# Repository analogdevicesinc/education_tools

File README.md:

# ADI Educational Content

[Analog Devices Inc.](https://www.analog.com/en/index.html)

Resource files for applications/examples with Active Learning Modules [ADALM1000](https://www.analog.com/en/design-center/evaluation-hardware-and-software/evaluation-boards-kits/adalm1000.html), [ADALM2000](https://www.analog.com/en/design-center/evaluation-hardware-and-software/evaluation-boards-kits/adalm2000.html), [ADALM-PLUTO](https://www.analog.com/en/design-center/evaluation-hardware-and-software/evaluation-boards-kits/adalm-pluto.html) and [ADALP2000](https://www.analog.com/en/design-center/evaluation-hardware-and-software/evaluation-boards-kits/EVAL-ADALP2000.html) Parts Kit.

Most of the files are linked as archives to the activities available in the [Analog Devices Engineering University Program](https://wiki.analog.com/university).

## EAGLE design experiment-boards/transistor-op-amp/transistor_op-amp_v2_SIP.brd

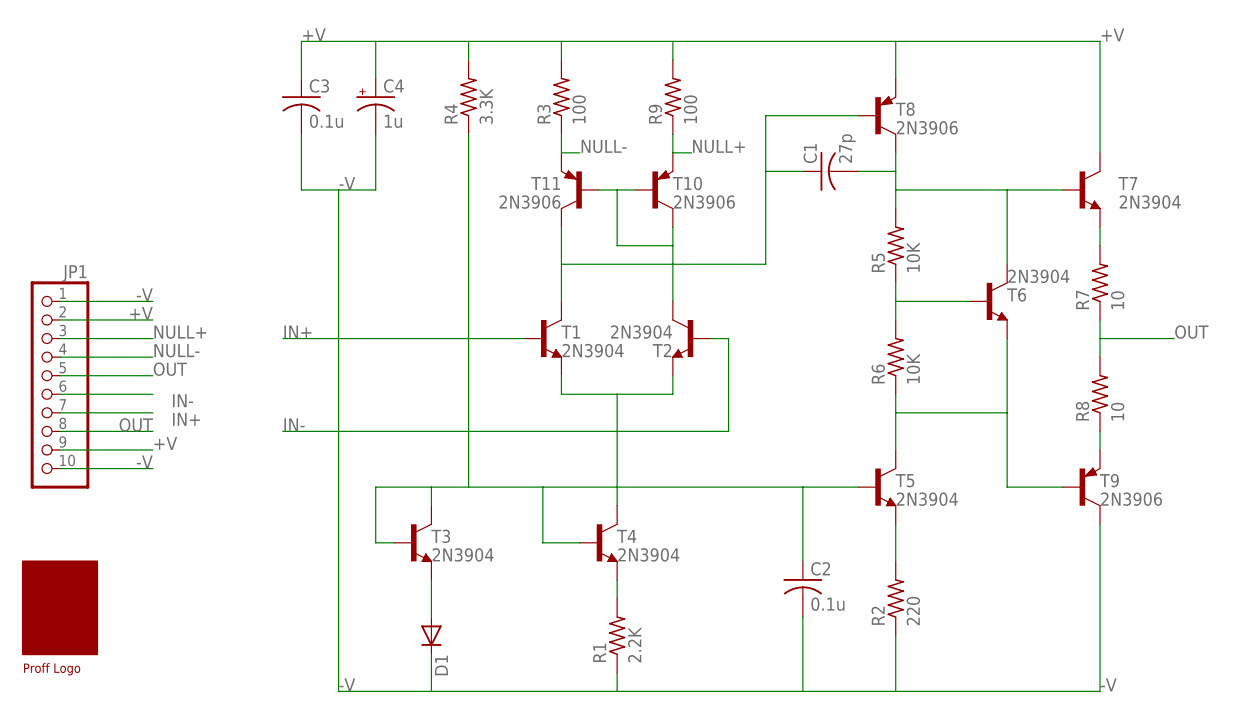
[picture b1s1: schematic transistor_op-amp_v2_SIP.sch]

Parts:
C1: 27p; C050-024X044
C2, C3: 0.1u; C050-024X044
C4: 1u; E2,5-5
D1: DIODE-D-7.5; D-7.5
JP1: PINHD-1X10; 1X10
R1: 2.2K; 0207/7
R2: 220; 0207/7
R3, R9: 100; 0207/7
R4: 3.3K; 0207/7
R5, R6: 10K; 0207/7
R7, R8: 10; 0207/7
T1, T2, T3, T4, T5, T6, T7: 2N3904; TO92
T8, T9, T10, T11: 2N3906; TO92
U$1: PROFF

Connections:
+V: C3.1, C4.+, JP1.2, JP1.9, R3.2, R4.2, R9.2, T7.1 (C), T8.3 (E)
-V: C2.2, C3.2, C4.-, D1.C, JP1.1, JP1.10, R1.1, R2.1, T9.1 (C)
IN+: JP1.6, T1.2 (B)
IN-: JP1.7, T2.2 (B)
unnamed: D1.A, T3.3 (E)
unnamed: C2.1, R4.1, T3.1 (C), T3.2 (B), T4.2 (B), T5.2 (B)
unnamed: R1.2, T4.3 (E)
unnamed: R2.2, T5.3 (E)
unnamed: T1.3 (E), T2.3 (E), T4.1 (C)
unnamed: R7.2, T7.3 (E)
unnamed: R6.1, T5.1 (C), T6.3 (E), T9.2 (B)
unnamed: R5.1, R6.2, T6.2 (B)
unnamed: C1.2, R5.2, T6.1 (C), T7.2 (B), T8.1 (C)
unnamed: R8.1, T9.3 (E)
unnamed: C1.1, T1.1 (C), T8.2 (B), T11.1 (C)
unnamed: T2.1 (C), T10.1 (C), T10.2 (B), T11.2 (B)
NULL+: JP1.3, R9.1, T10.3 (E)
NULL-: JP1.4, R3.1, T11.3 (E)
OUT: JP1.5, JP1.8, R7.1, R8.2

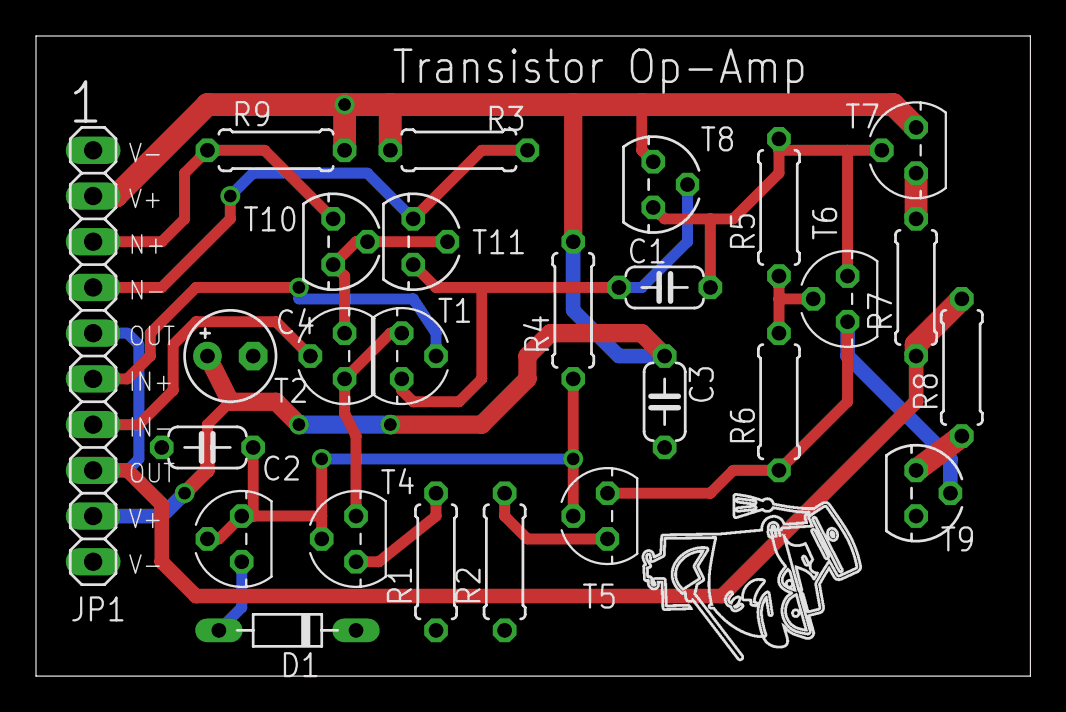
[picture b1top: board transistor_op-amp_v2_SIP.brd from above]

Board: 2 copper layers, 55.2 x 35.6 mm, 27 parts (0 on the bottom side), 19 nets.

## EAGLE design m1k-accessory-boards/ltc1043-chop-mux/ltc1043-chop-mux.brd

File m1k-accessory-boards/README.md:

# ADALM1000 Accessory Boards

[Analog Devices Inc.](https://www.analog.com/en/index.html)

Design Resource files for accessory PC boards for use with Active Learning Module [ADALM1000](https://www.analog.com/en/design-center/evaluation-hardware-and-software/evaluation-boards-kits/adalm1000.html), [ADALP2000](https://www.analog.com/en/design-center/evaluation-hardware-and-software/evaluation-boards-kits/EVAL-ADALP2000.html) Parts Kit.

The PC Board design files were generated using EAGLE (Easily Applicable Graphical Layout Editor) Version 7.7.0 for Windows (64 bit) Standard Edition.

The board files can generally be downloaded and used directly on many prototyping and rapid PC board manufacturer web sites. [Oshpark](https://oshpark.com/):

General background on the M1K accessory boards.

The idea is that the M1K analog input path is bare bones simple (for cost savings) and this ecosystem of accessory boards is a set of signal chain building blocks to daisy chain together more complex input and output signal chains. To that end there are generally pass through connections from one side of the boards to the other. Let's consider the 8 pin female analog connector on the M1K as connector "analog1". The connector pads on the accessory boards named ADALM1000 would be populated with matching male connectors. The connector pads on the accessory boards named analog2 would be populated with a female connector replicating the female connector on the M1K but with whatever signal processing a given board does inserted. The simple model is that various boards would be daisy chained in series (the ADALM1000 male connector plugged into the analog2 female connector etc.) building up a new signal chain. The order the boards are connected in series would of course matter and provides additional flexibility. What is not yet there in the initial release is what we are calling a "riser" board which allows the signal chain to split vertically and have a second parallel path as it were.

- Applications:
  - Analog Input Multiplexer using CD4052 dual 4:1
  - Input Buffer amplifier using dual op-amp footprint such as AD822 and AD8542
  - Input Buffer amplifier using single op-amp footprints
  - Input resistor voltage divider
  - Floating Amp meter / Milli-ohm meter
  - BNC / Scope probe adapter
  - +/- 5 V supply generator
    - Notice that the M1K connector has two ground pins. The -5 generator hijacks one of these pins for its -5 V rail. On all the accessory boards these two "ground" pins are never shorted together. If a given board (other than the -5 generator) is plugged into the M1K directly, the two pins will be connected together inside the M1K.
  - AWG quad op-amp buffer
  - Second order active filter
  - Test point extender board
  - Right angle extender board
  - Dip Switch extender board

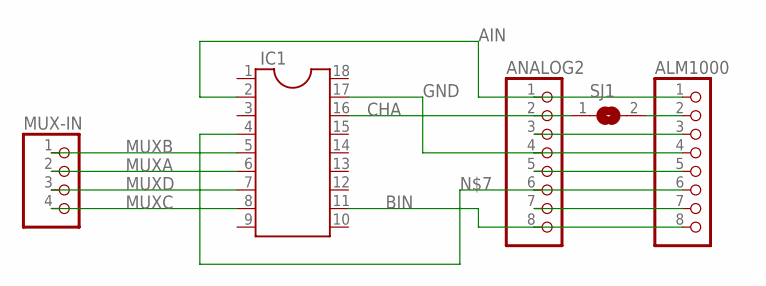
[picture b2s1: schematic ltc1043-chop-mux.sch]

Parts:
ALM1000: PINHD-1X8; 1X08
ANALOG2: PINHD-1X8; 1X08
IC1: DIL18
MUX-IN: PINHD-1X4; 1X04
SJ1: SJ

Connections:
AIN: ALM1000.1, ANALOG2.1, IC1.2
BIN: ALM1000.8, ANALOG2.8, IC1.11
CHA: ANALOG2.2, IC1.16, SJ1.1
GND: ALM1000.4, ANALOG2.4, IC1.17
MUXA: IC1.6, MUX-IN.2
MUXB: IC1.5, MUX-IN.1
MUXC: IC1.8, MUX-IN.4
MUXD: IC1.7, MUX-IN.3
unnamed: ALM1000.2, SJ1.2
unnamed: ALM1000.7, ANALOG2.7
unnamed: ALM1000.6, ANALOG2.6, IC1.4
unnamed: ALM1000.5, ANALOG2.5
unnamed: ALM1000.3, ANALOG2.3

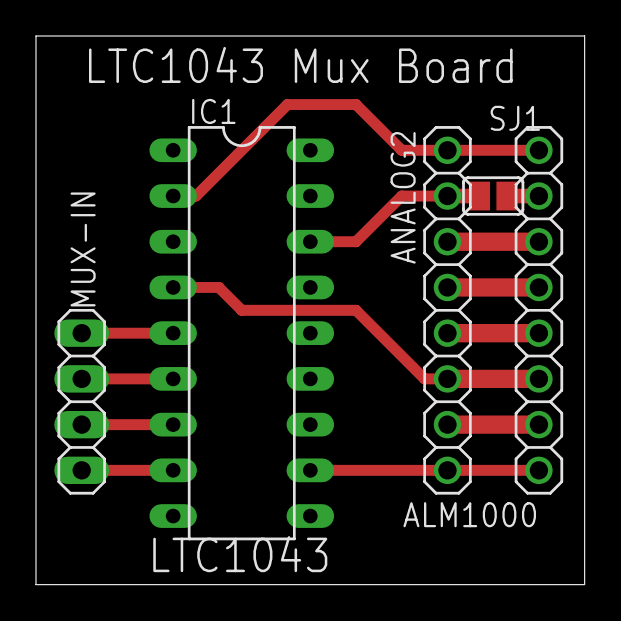
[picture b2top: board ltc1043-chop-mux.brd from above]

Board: 2 copper layers, 30.5 x 30.5 mm, 5 parts (0 on the bottom side), 13 nets.

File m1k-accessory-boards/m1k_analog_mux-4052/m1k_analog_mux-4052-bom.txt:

Partlist exported from m1k_analog_mux-4052.sch at 4/23/2020 8:47 AM

Part    Value   Device      Package Description                       
ALM1000         PINHD-1X8   1X08    PIN HEADER                        
ANALOG2         PINHD-1X8   1X08    PIN HEADER                        
CTRL            PINHD-1X3   1X03    PIN HEADER                        
IC1     CD4052N CD4052N     DIL16   Dual 4-channel ANALOG MULTIPLEXER 
MUXIN           PINHD-1X8   1X08    PIN HEADER

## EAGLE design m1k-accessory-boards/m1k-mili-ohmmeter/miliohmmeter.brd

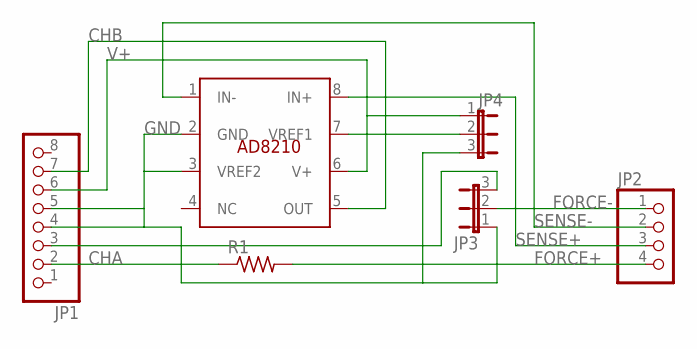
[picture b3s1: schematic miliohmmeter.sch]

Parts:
JP1: PINHD-1X8; 1X08
JP2: PINHD-1X4; 1X04
JP3, JP4: JP2E; JP2
R1: R-US_0207/10; 0207/10
U1: AD8210; SO8

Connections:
CHA: JP1.2, R1.1
CHB: JP1.7, U1.5 (OUT)
FORCE+: JP2.4, R1.2
FORCE-: JP2.1, JP3.2
GND: JP1.4, JP1.5, JP3.1, JP4.3, U1.2 (GND), U1.3 (VREF2)
unnamed: JP1.3, JP3.3
unnamed: JP4.2, U1.7 (VREF1)
SENSE+: JP2.3, U1.8 (IN+)
SENSE-: JP2.2, U1.1 (IN-)
V+: JP1.6, JP4.1, U1.6 (V+)

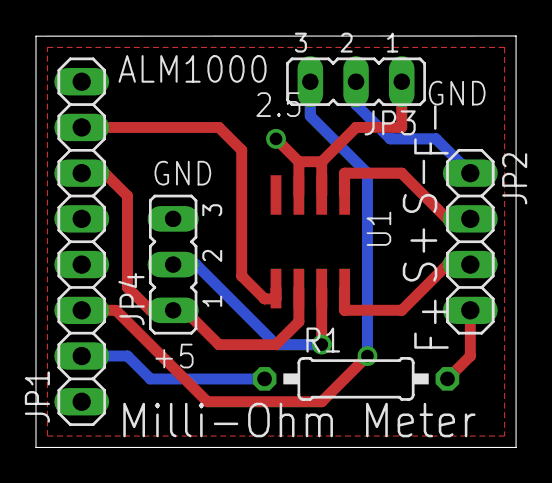
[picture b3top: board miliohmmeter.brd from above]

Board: 2 copper layers, 26.7 x 22.9 mm, 6 parts (0 on the bottom side), 10 nets.

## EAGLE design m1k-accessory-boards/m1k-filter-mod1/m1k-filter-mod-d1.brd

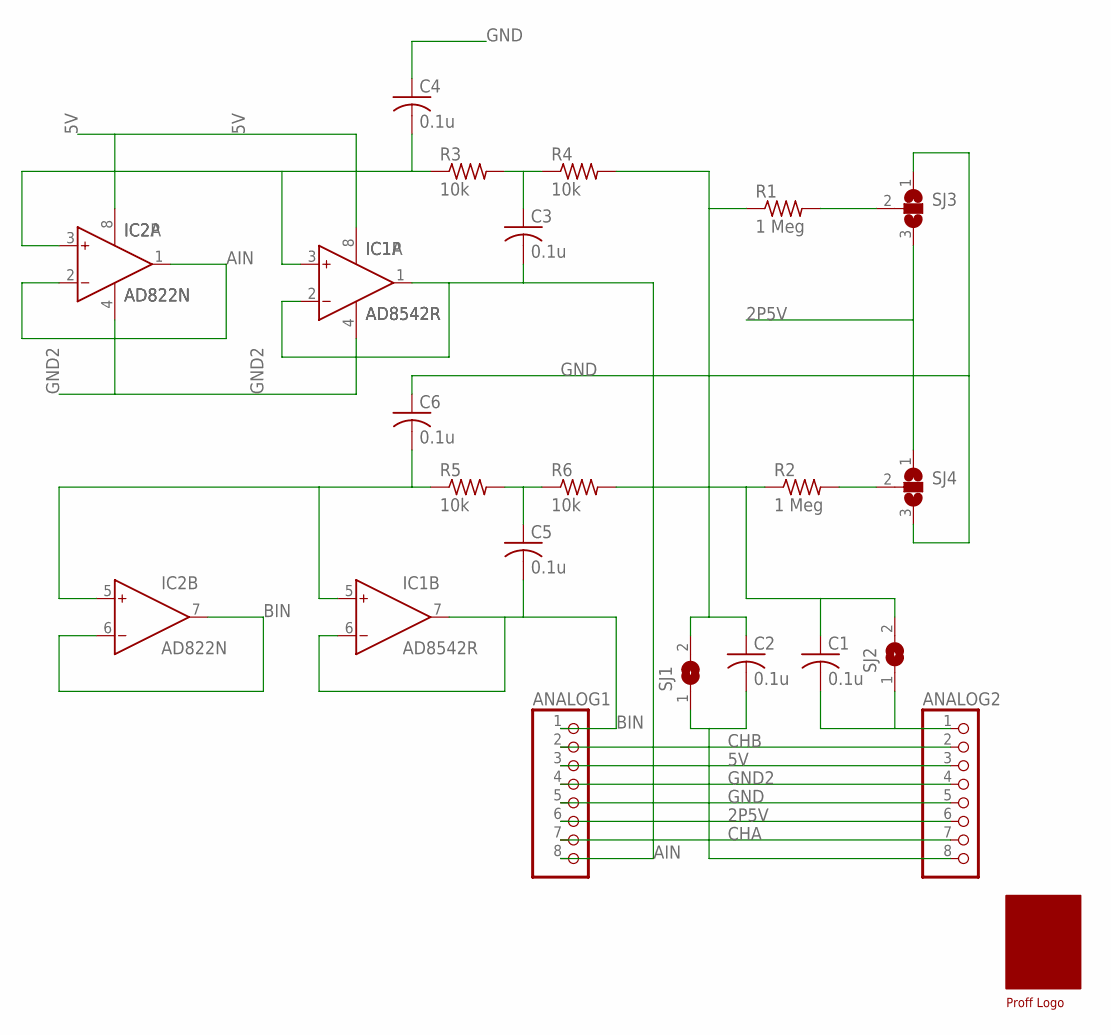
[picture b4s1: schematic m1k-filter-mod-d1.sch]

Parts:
ANALOG1, ANALOG2: PINHD-1X8; 1X08
C1, C2, C3, C4, C5, C6: 0.1u; C050-024X044
IC1: AD8542R; SO8
IC2: AD822N; DIL08
R1, R2: 1 Meg; 0204/7
R3, R4, R5, R6: 10k; 0204/7
SJ1, SJ2: SJ
SJ3, SJ4: SJ2W; SJ_2
U$1: PROFF

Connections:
2P5V: ANALOG1.6, ANALOG2.6, SJ3.3, SJ4.1
5V: ANALOG1.3, ANALOG2.3, IC1.8 (V+), IC2.8 (V+)
AIN: ANALOG1.8, C3.2, IC1.1 (OUT), IC1.2 (IN-), IC2.1 (OUT), IC2.2 (IN-)
BIN: ANALOG1.1, C5.2, IC1.6 (IN-), IC1.7 (OUT), IC2.6 (IN-), IC2.7 (OUT)
CHA: ANALOG1.7, ANALOG2.7
CHB: ANALOG1.2, ANALOG2.2
GND: ANALOG1.5, ANALOG2.5, C4.1, C6.1, SJ3.1, SJ4.3
GND2: ANALOG1.4, ANALOG2.4, IC1.4 (V-), IC2.4 (V-)
unnamed: ANALOG2.1, C1.2, SJ2.1
unnamed: R1.2, SJ3.2
unnamed: ANALOG2.8, C2.2, SJ1.1
unnamed: C3.1, R3.2, R4.1
unnamed: C2.1, R1.1, R4.2, SJ1.2
unnamed: C1.1, R2.1, R6.2, SJ2.2
unnamed: C6.2, IC1.5 (IN+), IC2.5 (IN+), R5.1
unnamed: C5.1, R5.2, R6.1
unnamed: C4.2, IC1.3 (IN+), IC2.3 (IN+), R3.1
unnamed: R2.2, SJ4.2

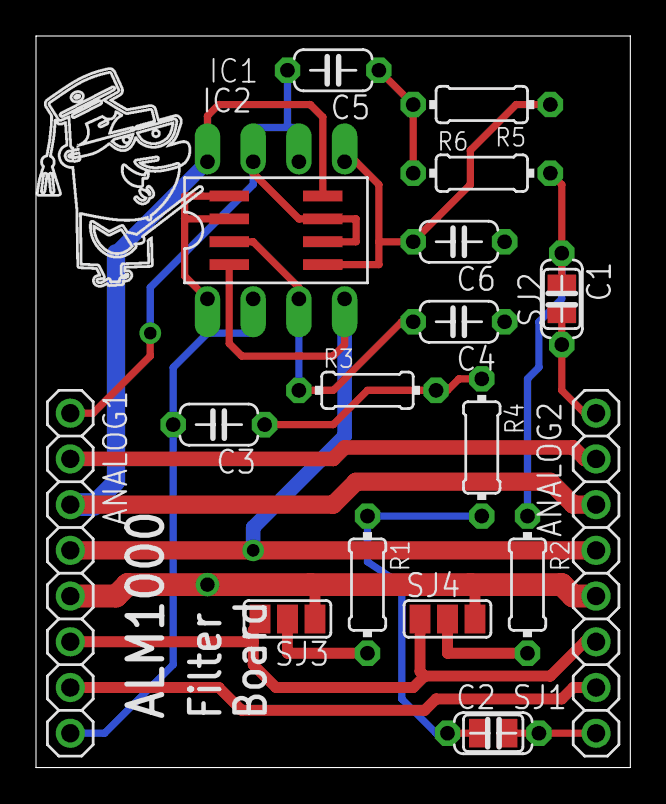
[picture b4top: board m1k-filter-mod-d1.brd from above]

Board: 2 copper layers, 33.0 x 40.6 mm, 21 parts (0 on the bottom side), 18 nets.

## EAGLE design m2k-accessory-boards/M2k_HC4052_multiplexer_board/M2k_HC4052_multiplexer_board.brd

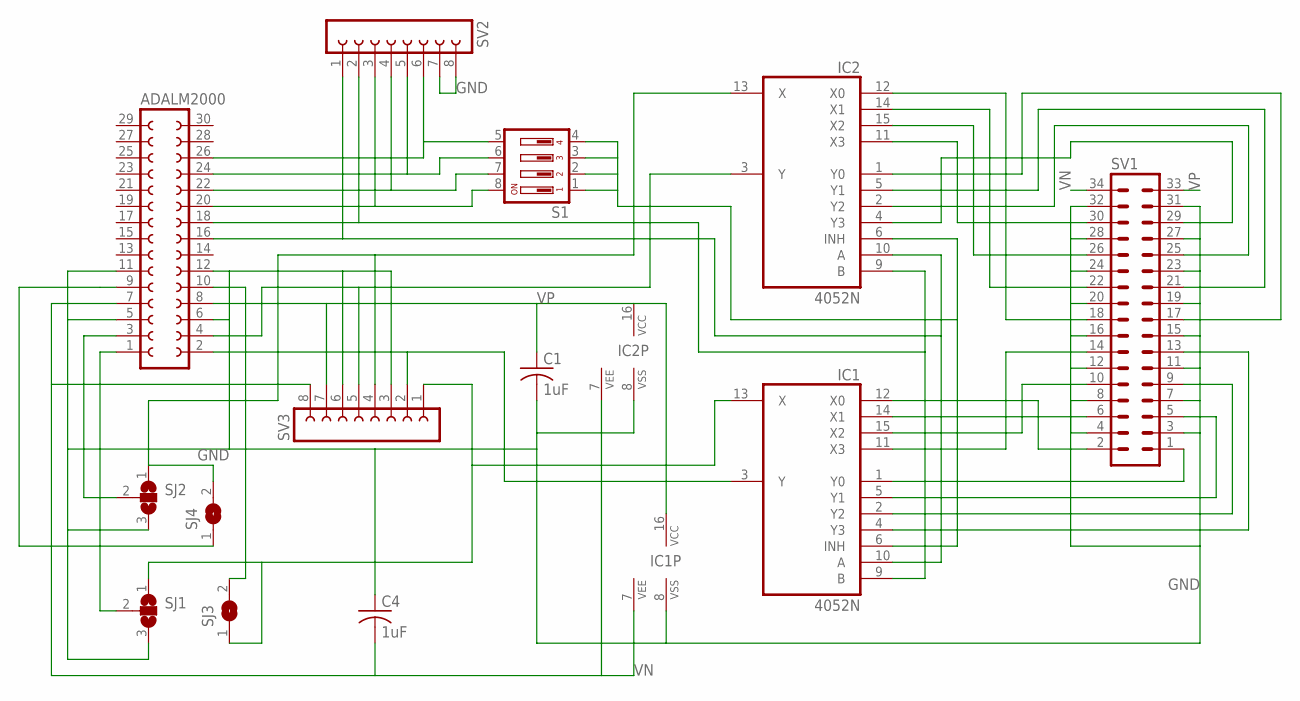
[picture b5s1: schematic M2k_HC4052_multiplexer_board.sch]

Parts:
ADALM2000: FE15-2
C1, C4: 1uF; C050-024X044
IC1, IC2: 4052N; DIL16
S1: DIP04YL
SJ1, SJ2: SJ2W; SJ_2
SJ3, SJ4: SJ
SV1: MA17-2
SV2, SV3: FE08-1; FE08

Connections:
ES: IC1.13 (X), SJ1.1, SJ3.1, SV3.1
GND: ADALM2000.5, ADALM2000.6, ADALM2000.11, ADALM2000.12, C1.2, C4.1, IC1.8 (VSS), IC2.8 (VSS), SJ1.3, SJ2.3, SV1.3, SV1.4, SV1.7, SV1.8, SV1.11, SV1.12, SV1.15, SV1.16, SV1.19, SV1.20, SV1.23, SV1.24, SV1.27, SV1.28, SV1.31, SV1.32, SV2.7, SV2.8, SV3.3, SV3.6
unnamed: ADALM2000.26, S1.5, SV2.6
unnamed: IC1.12 (X0), SV1.2
unnamed: IC1.6 (INH), IC2.6 (INH), S1.1, S1.2, S1.3, S1.4
unnamed: ADALM2000.2, IC1.3 (Y), SV3.2
unnamed: IC1.1 (Y0), SV1.1
unnamed: IC1.14 (X1), SV1.6
unnamed: IC2.13 (X), SJ2.1, SJ4.2, SV3.4
unnamed: IC1.5 (Y1), SV1.5
unnamed: IC1.15 (X2), SV1.10
unnamed: ADALM2000.4, IC2.3 (Y), SV3.5
unnamed: ADALM2000.16, IC1.10 (A), IC2.10 (A), SV2.1
unnamed: ADALM2000.18, IC1.9 (B), IC2.9 (B), SV2.2
unnamed: IC1.11 (X3), SV1.14
unnamed: IC1.2 (Y2), SV1.9
unnamed: IC1.4 (Y3), SV1.13
unnamed: IC2.12 (X0), SV1.18
unnamed: IC2.14 (X1), SV1.22
unnamed: IC2.15 (X2), SV1.26
unnamed: IC2.11 (X3), SV1.30
unnamed: IC2.1 (Y0), SV1.17
unnamed: IC2.5 (Y1), SV1.21
unnamed: IC2.2 (Y2), SV1.25
unnamed: IC2.4 (Y3), SV1.29
unnamed: ADALM2000.1, SJ1.2
unnamed: ADALM2000.3, SJ2.2
unnamed: ADALM2000.20, S1.8, SV2.3
unnamed: ADALM2000.22, S1.7, SV2.4
unnamed: ADALM2000.24, S1.6, SV2.5
VN: ADALM2000.7, C4.2, IC1.7 (VEE), IC2.7 (VEE), SV1.34, SV3.8
VP: ADALM2000.8, C1.1, IC1.16 (VCC), IC2.16 (VCC), SV1.33, SV3.7
W1: ADALM2000.10, SJ3.2
W2: ADALM2000.9, SJ4.1

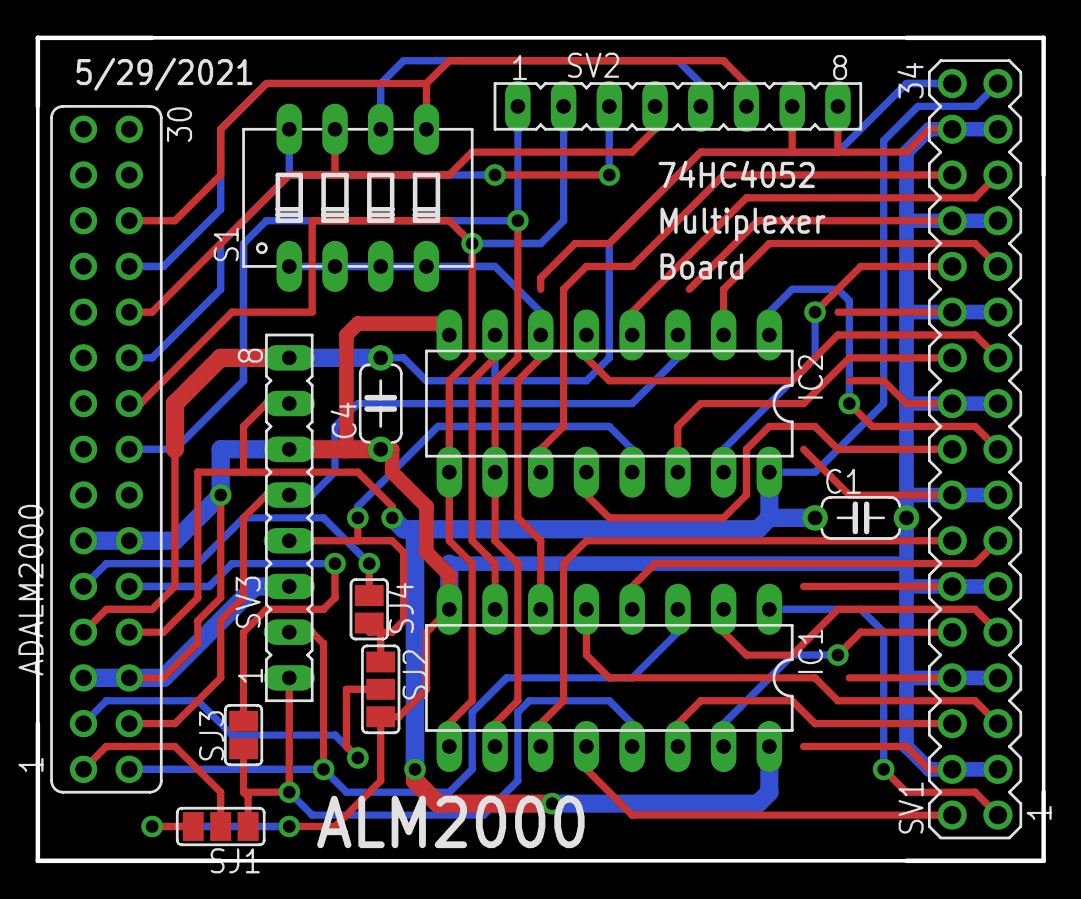
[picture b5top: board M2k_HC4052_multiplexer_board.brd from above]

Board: 2 copper layers, 55.9 x 45.7 mm, 13 parts (0 on the bottom side), 34 nets.

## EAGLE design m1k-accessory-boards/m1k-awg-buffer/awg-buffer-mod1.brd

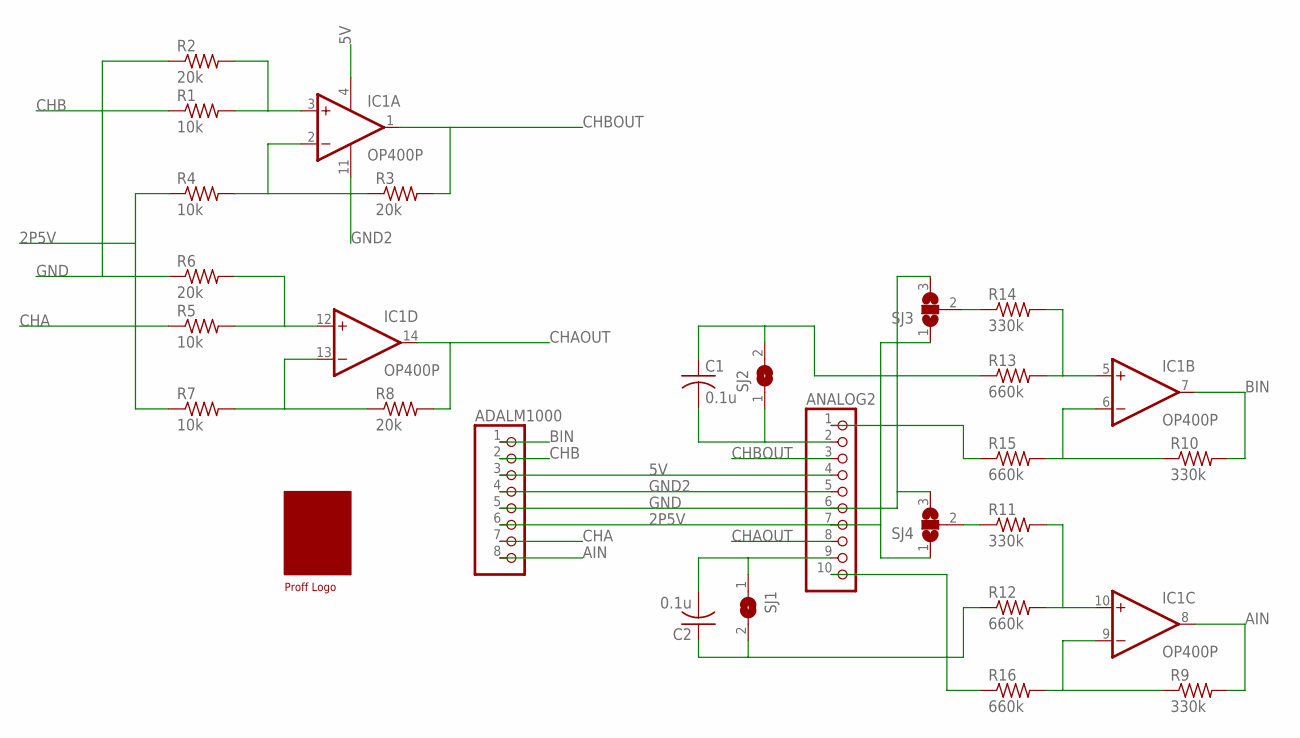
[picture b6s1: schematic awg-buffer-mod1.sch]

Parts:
ADALM1000: PINHD-1X8; 1X08
ANALOG2: PINHD-1X10; 1X10
C1, C2: 0.1u; C050-024X044
IC1: OP400P; DIL14
R1, R4, R5, R7: 10k; 0204/7
R2, R3, R6, R8: 20k; 0204/7
R9, R10, R11, R14: 330k; 0204/7
R12, R13, R15, R16: 660k; 0204/7
SJ1, SJ2: SJ
SJ3, SJ4: SJ2W; SJ_2
U$1: PROFF

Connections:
2P5V: ADALM1000.6, ANALOG2.7, R4.1, R7.1, SJ3.1, SJ4.1
5V: ADALM1000.3, ANALOG2.4, IC1.4 (V+)
AIN: ADALM1000.8, IC1.8 (OUT), R9.2
BIN: ADALM1000.1, IC1.7 (OUT), R10.2
CHA: ADALM1000.7, R5.1
CHAOUT: ANALOG2.8, IC1.14 (OUT), R8.2
CHB: ADALM1000.2, R1.1
CHBOUT: ANALOG2.3, IC1.1 (OUT), R3.2
GND: ADALM1000.5, ANALOG2.6, R2.1, R6.1, SJ3.3, SJ4.3
GND2: ADALM1000.4, ANALOG2.5, IC1.11 (V-)
unnamed: ANALOG2.2, C1.2, SJ2.1
unnamed: IC1.10 (+IN), R11.2, R12.2
unnamed: ANALOG2.9, C2.2, SJ1.1
unnamed: IC1.9 (-IN), R9.1, R16.2
unnamed: C2.1, R12.1, SJ1.2
unnamed: C1.1, R13.1, SJ2.2
unnamed: IC1.6 (-IN), R10.1, R15.2
unnamed: IC1.2 (-IN), R3.1, R4.2
unnamed: IC1.13 (-IN), R7.2, R8.1
unnamed: IC1.3 (+IN), R1.2, R2.2
unnamed: IC1.12 (+IN), R5.2, R6.2
unnamed: IC1.5 (+IN), R13.2, R14.2
unnamed: ANALOG2.1, R15.1
unnamed: ANALOG2.10, R16.1
unnamed: R14.1, SJ3.2
unnamed: R11.1, SJ4.2

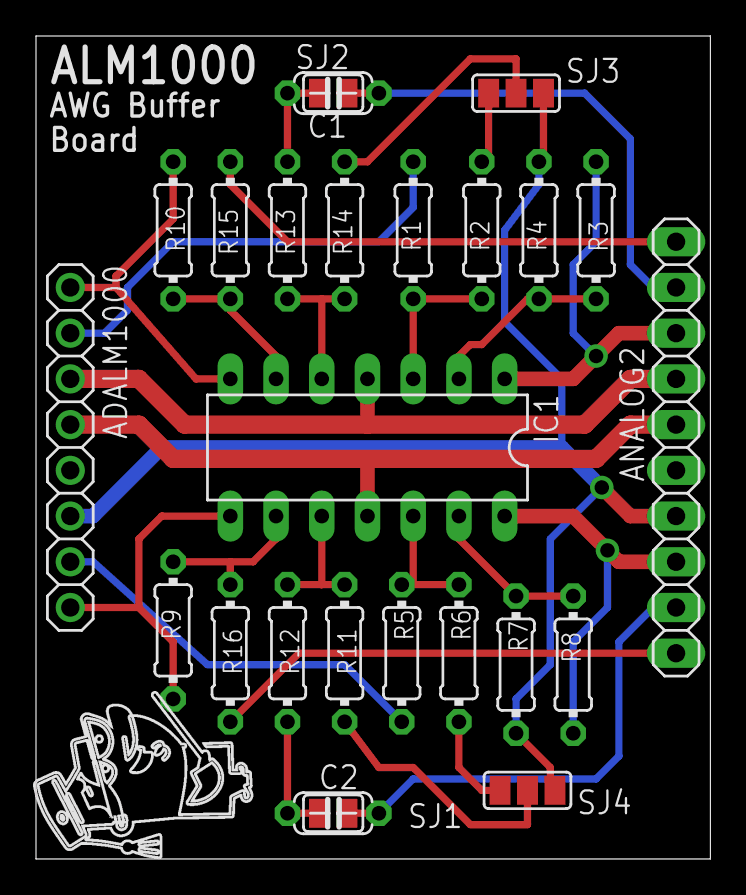
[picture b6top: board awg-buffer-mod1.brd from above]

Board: 2 copper layers, 37.5 x 45.7 mm, 26 parts (0 on the bottom side), 26 nets.

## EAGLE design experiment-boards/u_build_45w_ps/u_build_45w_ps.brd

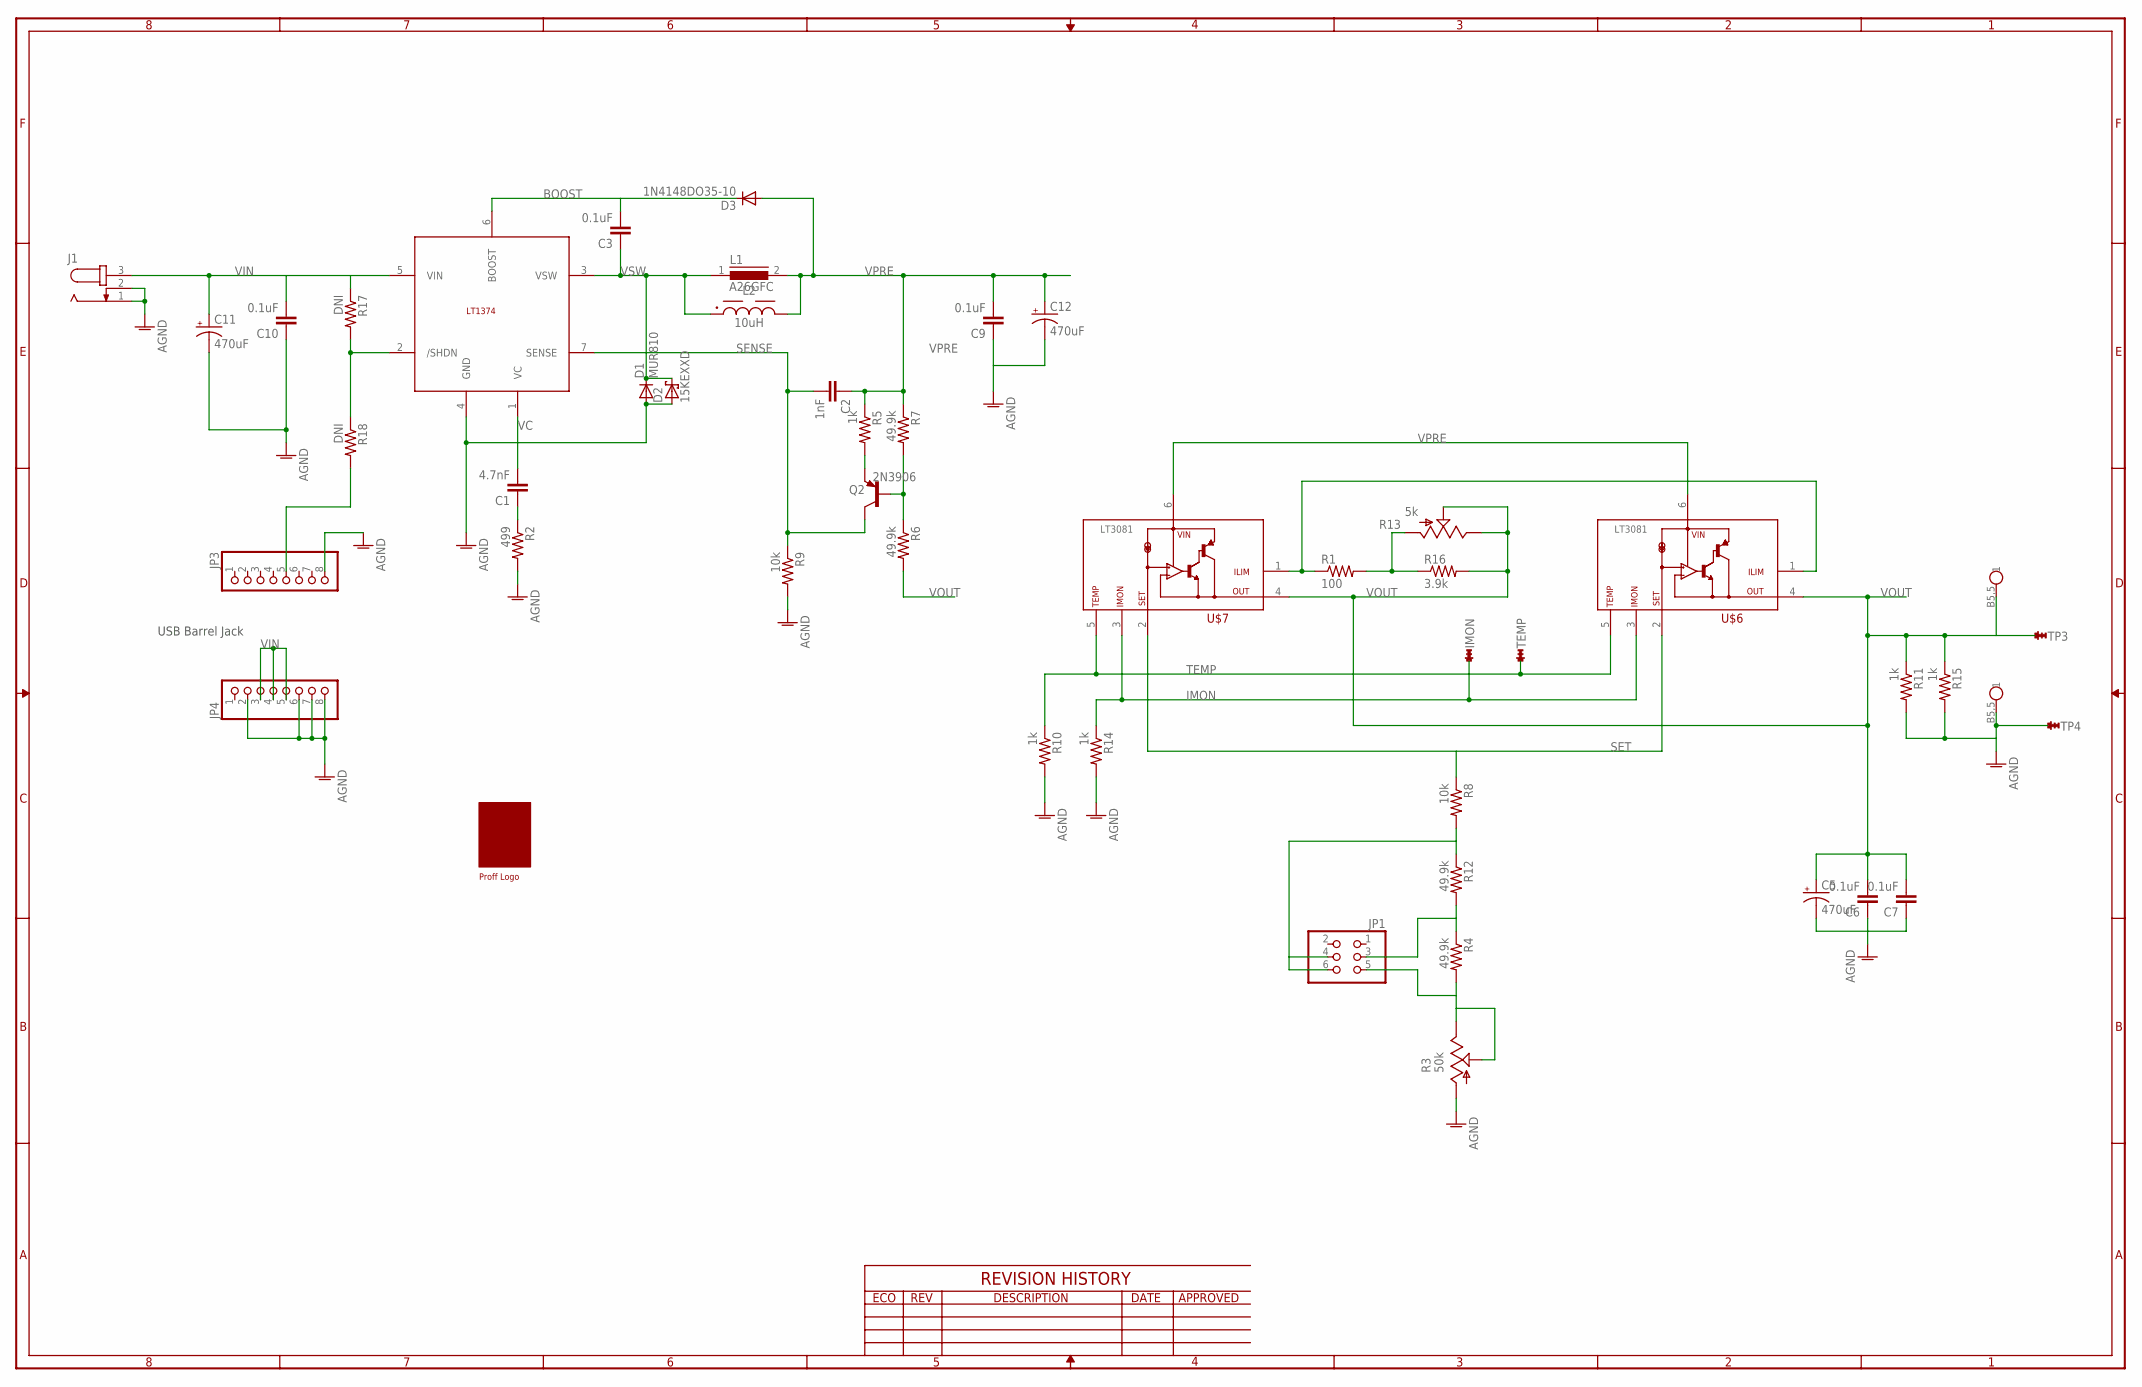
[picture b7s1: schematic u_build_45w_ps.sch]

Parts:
C1: 4.7nF; C050-025X075
C2: 1nF; C050-025X075
C3: 0.1uF; C050-025X075
C5, C11, C12: 470uF; E5-10,5
C6, C7, C9, C10: 0.1uF; C050-045X075
D1: MUR810; TO220ACS
D2: 15KEXXD; DO201T15
D3: 1N4148DO35-10; DO35-10
IC2: LT1374TO220-7; LT3081
IMON: TURRET0.092; TURRET_MILLMAX_2501-2
J1: JACK-PLUG0; SPC4077
J5, J6: BAN_JACK1; PC_BAN_JACK
JP1: PINHD-2X3; 2X03
JP3, JP4: PINHD-1X8; 1X08
L1: A26GFC
L2: 10uH; WE-TIS_1111
Q2: 2N3906; TO92
R1: 100; 0207/10
R2: 499; 0207/10
R3: 50k; RS3
R4, R6, R7, R12: 49.9k; 0207/10
R5, R10, R11, R14, R15: 1k; 0207/10
R8, R9: 10k; 0207/10
R13: 5k; RS3
R16: 3.9k; 0207/10
R17, R18: DNI; 0207/10
TEMP: TURRET0.092; TURRET_MILLMAX_2501-2
TP3, TP4: TURRET0.092; TURRET_MILLMAX_2501-2
U$1: PROFF
U$6, U$7: LT3081

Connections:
AGND: C5.-, C6.1, C7.1, C9.1, C10.1, C11.-, C12.-, D1.A, D2.A, IC2.4 (GND), J1.1, J1.2, J6.B5,5, JP3.8, JP4.2, JP4.6, JP4.7, JP4.8, R2.2, R3.A, R9.2, R10.2, R11.2, R14.2, R15.2, TP4.1
BOOST: C3.2, D3.C, IC2.6 (BOOST)
ILIM: R1.1, U$6.1 (ILIM), U$7.1 (ILIM)
IMON: IMON.1, R14.1, U$6.3 (IMON), U$7.3 (IMON)
unnamed: C1.1, R2.1
unnamed: IC2.2 (/SHDN), R17.2, R18.1
unnamed: JP1.5, R3.E, R3.S, R4.2
unnamed: JP1.3, R4.1, R12.2
unnamed: R1.2, R13.A, R16.1
unnamed: JP3.5, R18.2
unnamed: JP1.4, JP1.6, R8.2, R12.1
unnamed: Q2.2 (B), R6.1, R7.2
unnamed: Q2.3 (E), R5.2
SENSE: C2.2, IC2.7 (SENSE), Q2.1 (C), R9.1
SET: R8.1, U$6.2 (SET), U$7.2 (SET)
TEMP: R10.1, TEMP.1, U$6.5 (TEMP), U$7.5 (TEMP)
VC: C1.2, IC2.1 (VC)
VIN: C10.2, C11.+, IC2.5 (VIN), J1.3, JP4.3, JP4.4, JP4.5, R17.1
VOUT: C5.+, C6.2, C7.2, J5.B5,5, R6.2, R11.1, R13.E, R13.S, R15.1, R16.2, TP3.1, U$6.4 (OUT), U$7.4 (OUT)
VPRE: C2.1, C9.2, C12.+, D3.A, L1.2, L2.2, R5.1, R7.1, U$6.6 (VIN), U$7.6 (VIN)
VSW: C3.1, D1.C, D2.C, IC2.3 (VSW), L1.1, L2.1

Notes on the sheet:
USB Barrel Jack

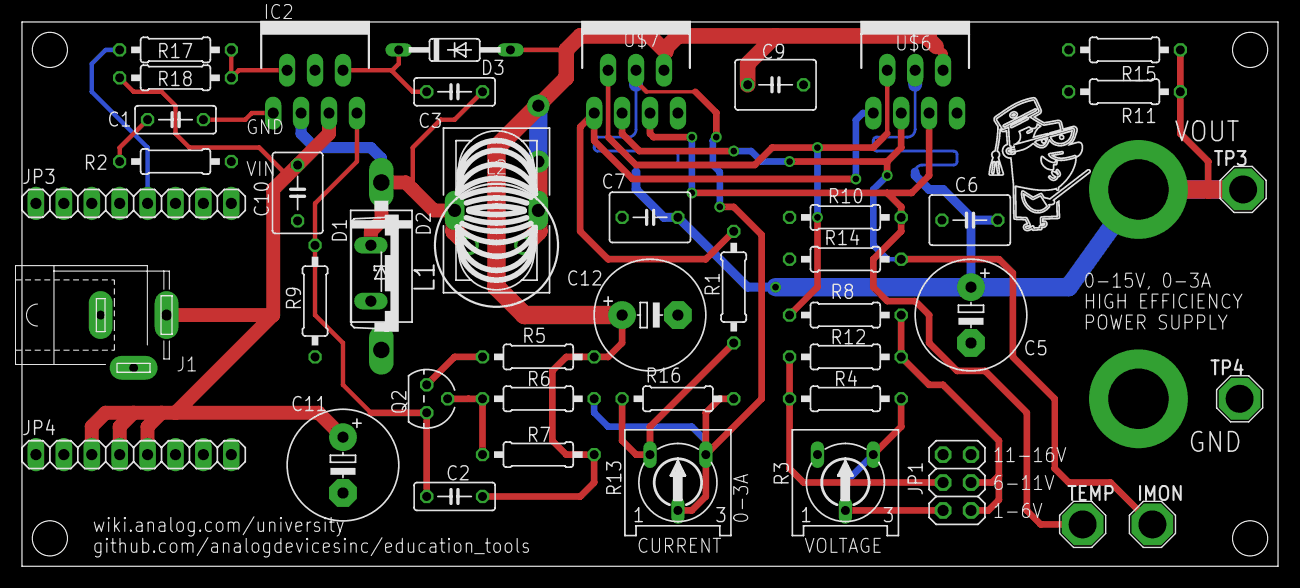
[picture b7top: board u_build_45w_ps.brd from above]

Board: 2 copper layers, 114.3 x 49.5 mm, 48 parts (0 on the bottom side), 21 nets.

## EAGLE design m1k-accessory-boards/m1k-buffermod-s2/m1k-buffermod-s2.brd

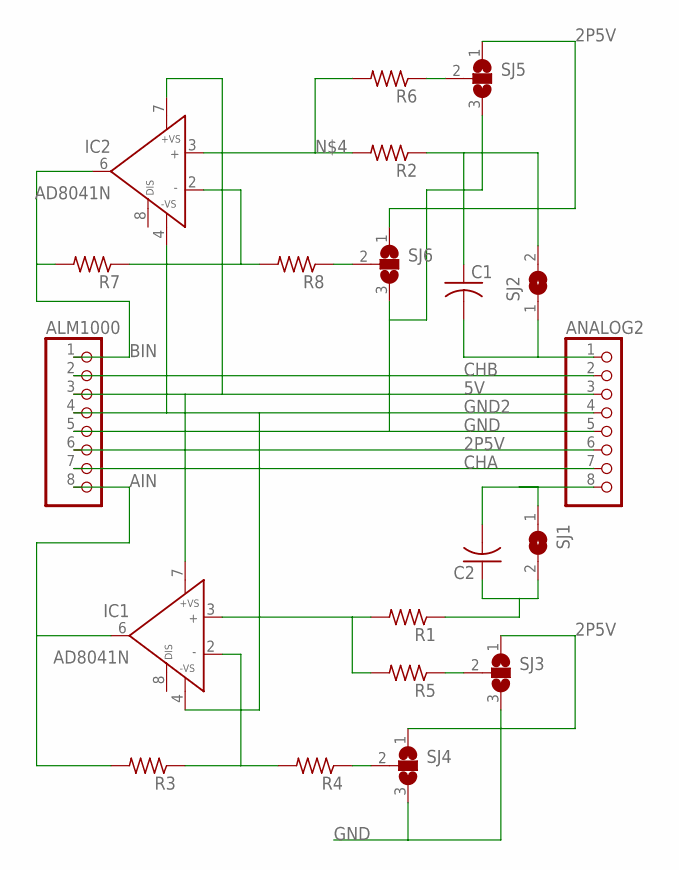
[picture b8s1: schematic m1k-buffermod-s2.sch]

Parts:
ALM1000: PINHD-1X8; 1X08
ANALOG2: PINHD-1X8; 1X08
C1, C2: C-US050-024X044; C050-024X044
IC1, IC2: AD8041N; DIL08
R1, R2, R3, R4, R5, R6, R7, R8: R-US_0204/7; 0204/7
SJ1, SJ2: SJ
SJ3, SJ4, SJ5, SJ6: SJ2W; SJ_2

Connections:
2P5V: ALM1000.6, ANALOG2.6, SJ3.1, SJ4.1, SJ5.1, SJ6.1
5V: ALM1000.3, ANALOG2.3, IC1.7 (+VS), IC2.7 (+VS)
AIN: ALM1000.8, IC1.6 (OUT), R3.2
BIN: ALM1000.1, IC2.6 (OUT), R7.2
CHA: ALM1000.7, ANALOG2.7
CHB: ALM1000.2, ANALOG2.2
GND: ALM1000.5, ANALOG2.5, SJ3.3, SJ4.3, SJ5.3, SJ6.3
GND2: ALM1000.4, ANALOG2.4, IC1.4 (-VS), IC2.4 (-VS)
unnamed: ANALOG2.1, C1.2, SJ2.1
unnamed: IC1.2 (IN-), R3.1, R4.2
unnamed: ANALOG2.8, C2.2, SJ1.1
unnamed: IC2.3 (IN+), R2.2, R6.2
unnamed: C2.1, R1.1, SJ1.2
unnamed: C1.1, R2.1, SJ2.2
unnamed: R4.1, SJ4.2
unnamed: R5.1, SJ3.2
unnamed: IC2.2 (IN-), R7.1, R8.2
unnamed: R6.1, SJ5.2
unnamed: IC1.3 (IN+), R1.2, R5.2
unnamed: R8.1, SJ6.2

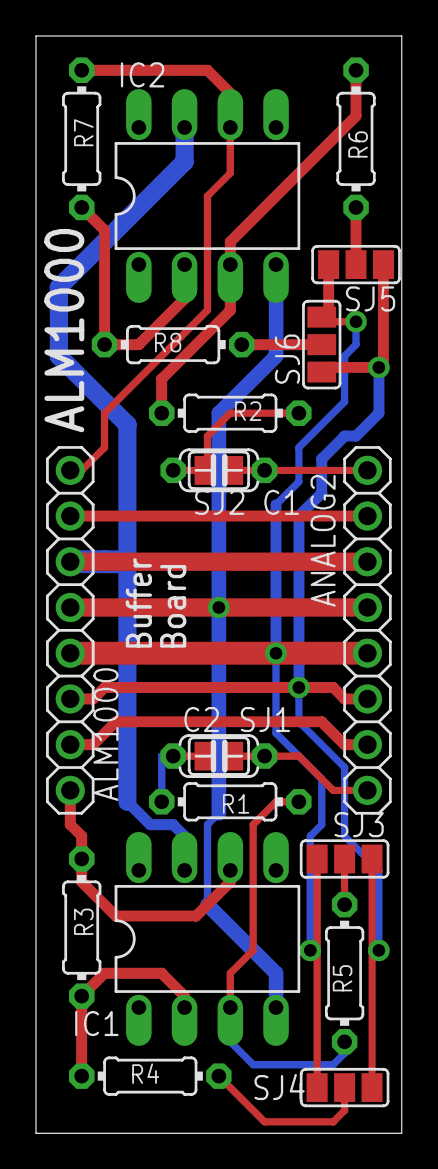
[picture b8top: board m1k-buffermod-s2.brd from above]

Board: 2 copper layers, 20.3 x 61.0 mm, 20 parts (0 on the bottom side), 20 nets.

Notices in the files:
parts and their libraries:
Eagle_WE-TIS: Copyright: Würth Elektronik
